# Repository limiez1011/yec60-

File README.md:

# yec60%

## Description
The yec60% keyboard is based on the ansi 60% layout and has 61 hotswappable sockets.

## Features
- Built in rp2040 MCU
- QMK firmware
- Hot swap sockets

## Flashing procedure
To flash firmware onto the RP2040 there are 2 pads under the "BOOT" text on the silkscreen, you must short those 2 pins to enter bootloader. Once in bootloader a drive should appear on your computer. Copy the .uf2 file from the QMK folder of the repo and paste it into the drive. Once done unplug the USB cable and plug it back in and it should be flashed.

## Credits
Credits to aio3 for his amazing tools for keyboard design, and his premade footprints. Some other people I'd love to thank is the QMK team which have created an amazing and easy to use system.

## BOM
|Name         |Purpose                        |Quantity|Total Cost (USD)|Link                                                                                                                                                                                                                                                                                                                                                                                                                                                                                                                                                                                                                                                                                            |Distributor|
|-------------|-------------------------------|--------|----------------|------------------------------------------------------------------------------------------------------------------------------------------------------------------------------------------------------------------------------------------------------------------------------------------------------------------------------------------------------------------------------------------------------------------------------------------------------------------------------------------------------------------------------------------------------------------------------------------------------------------------------------------------------------------------------------------------|-----------|
|stabilizers  |stabilizing                    |1       |11.00           |https://www.aliexpress.com/item/1005004229140548.html?spm=a2g0o.productlist.main.6.3e4b4e91M4QOD4&algo_pvid=52c0f35d-5f37-4dcc-980f-3d382011e670&pdp_ext_f=%7B%22order%22%3A%22103%22%2C%22spu_best_type%22%3A%22price%22%2C%22eval%22%3A%221%22%2C%22fromPage%22%3A%22search%22%7D&utparam-url=scene%3Asearch%7Cquery_from%3A%7Cx_object_id%3A1005004229140548%7C_p_origin_prod%3A                                                                                                                                                                                                                                                                                                             |aliexpress |
|keycaps      |keycaps                        |1       |16.50           |https://www.aliexpress.com/item/1005009426980407.html?spm=a2g0o.detail.pcDetailTopMoreOtherSeller.11.e5e56b47W8lzpD&gps-id=pcDetailTopMoreOtherSeller&scm=1007.40050.354490.0&scm_id=1007.40050.354490.0&scm-url=1007.40050.354490.0&pvid=6ae83b90-ce64-454f-894f-8b7744045ac3&_t=gps-id%3ApcDetailTopMoreOtherSeller%2Cscm-url%3A1007.40050.354490.0%2Cpvid%3A6ae83b90-ce64-454f-894f-8b7744045ac3%2Ctpp_buckets%3A668%232846%238110%231995&pdp_ext_f=%7B%22order%22%3A%22510%22%2C%22eval%22%3A%221%22%2C%22sceneId%22%3A%2230050%22%2C%22fromPage%22%3A%22recommend%22%7D&utparam-url=scene%3ApcDetailTopMoreOtherSeller%7Cquery_from%3A%7Cx_object_id%3A1005009426980407%7C_p_origin_prod%3A|aliexpress |
|switches     |gateron milky yellow|70      |26.50           |https://www.aliexpress.com/item/1005007039372956.html?spm=a2g0o.cart.0.0.bc85452cwC4OF7&mp=1                                                                                                                                                                                                                                                                                                                                                                                                                                                                                                                                                                                                    |aliexpress |
|PCB          |pcb                            |5       |30.00           |                                                                                                                                                                                                                                                                                                                                                                                                                                                                                                                                                                                                                                                                                                |JLCPCB     |
|kalih sockets|hotswap                        |61      |3.00            |https://www.lcsc.com/product-detail/C41430893.html?spm=wm.gwc.xh.13.cbm___wm.mxq.ssl.gwc&lcsc_vid=T1lbU1RRQwVWUQcCQgcLA1UAEgBbAwBUFFheBFAFEVAxVlNRTlhWUVZTQlBXUjsOAxUeFF5JWBEPFBcWGBMaSQgFBAJABAsLWA%3D%3D                                                                                                                                                                                                                                                                                                                                                                                                                                                                                      |LCSC       |
|2mb flash    |storage                        |1       |1.50            |https://www.lcsc.com/product-detail/C2986331.html?spm=wm.mxq.bom.8.xh___wm.bjg.btn.cre&lcsc_vid=T1lbU1RRQwVWUQcCQgcLA1UAEgBbAwBUFFheBFAFEVAxVlNRTlhWUVZTQlBXUjsOAxUeFF5JWBEPFBcWGBMaSQgFBAJABAsLWA%3D%3D                                                                                                                                                                                                                                                                                                                                                                                                                                                                                        |LCSC       |
|PASSIVES     |PASSIVING                      |1       |8.50            |                                                                                                                                                                                                                                                                                                                                                                                                                                                                                                                                                                                                                                                                                                |LCSC       |
|DIODES       |NKEY ROLLOVER                  |61      |4.00            |https://www.lcsc.com/product-detail/C81598.html?spm=wm.mxq.bom.14.xh___wm.bjg.btn.cre&lcsc_vid=T1lbU1RRQwVWUQcCQgcLA1UAEgBbAwBUFFheBFAFEVAxVlNRTlhWUVZTQlBXUjsOAxUeFF5JWBEPFBcWGBMaSQgFBAJABAsLWA%3D%3D                                                                                                                                                                                                                                                                                                                                                                                                                                                                                         |LCSC       |
|XTAL         |CLOCK                          |1       |1.00            |https://www.lcsc.com/product-detail/C9002.html?spm=wm.mxq.bom.12.xh___wm.bjg.btn.cre&lcsc_vid=T1lbU1RRQwVWUQcCQgcLA1UAEgBbAwBUFFheBFAFEVAxVlNRTlhWUVZTQlBXUjsOAxUeFF5JWBEPFBcWGBMaSQgFBAJABAsLWA%3D%3D                                                                                                                                                                                                                                                                                                                                                                                                                                                                                          |LCSC       |
|USBC         |PORT                           |1       |1.00            |https://www.lcsc.com/product-detail/C165948.html?spm=wm.mxq.bom.10.xh___wm.bjg.btn.cre&lcsc_vid=T1lbU1RRQwVWUQcCQgcLA1UAEgBbAwBUFFheBFAFEVAxVlNRTlhWUVZTQlBXUjsOAxUeFF5JWBEPFBcWGBMaSQgFBAJABAsLWA%3D%3D                                                                                                                                                                                                                                                                                                                                                                                                                                                                                        |LCSC       |
|RP2040       |MCU                            |1       |1.00            |https://www.lcsc.com/product-detail/C2040.html?spm=wm.mxq.bom.8.xh___wm.bjg.btn.cre&lcsc_vid=T1lbU1RRQwVWUQcCQgcLA1UAEgBbAwBUFFheBFAFEVAxVlNRTlhWUVZTQlBXUjsOAxUeFF5JWBEPFBcWGBMaSQgFBAJABAsLWA%3D%3D                                                                                                                                                                                                                                                                                                                                                                                                                                                                                           |LCSC       |
|RT9013-33GB  |LDO                            |1       |1.00            |https://www.lcsc.com/product-detail/C47773.html?spm=wm.mxq.bom.9.xh___wm.bjg.btn.cre&lcsc_vid=T1lbU1RRQwVWUQcCQgcLA1UAEgBbAwBUFFheBFAFEVAxVlNRTlhWUVZTQlBXUjsOAxUeFF5JWBEPFBcWGBMaSQgFBAJABAsLWA%3D%3D                                                                                                                                                                                                                                                                                                                                                                                                                                                                                          |LCSC       |

## Photos

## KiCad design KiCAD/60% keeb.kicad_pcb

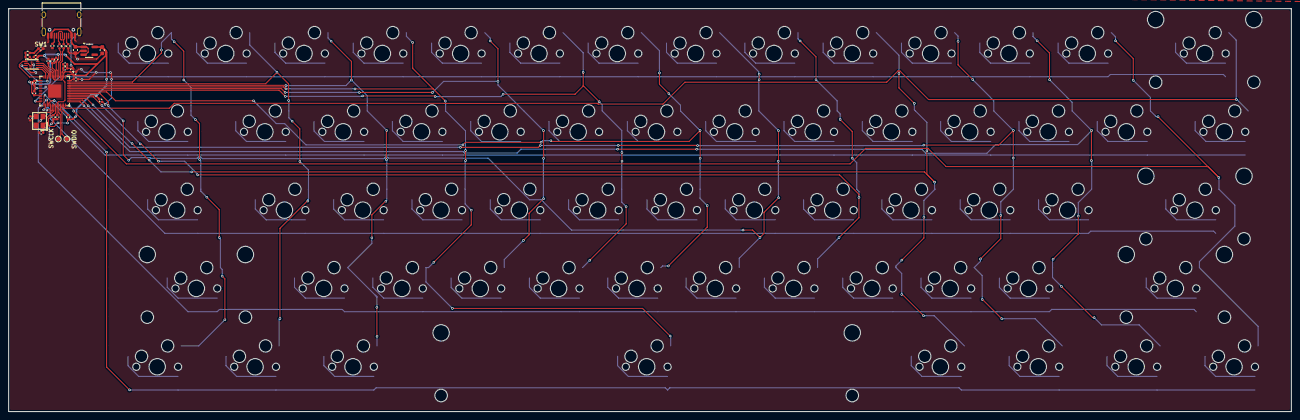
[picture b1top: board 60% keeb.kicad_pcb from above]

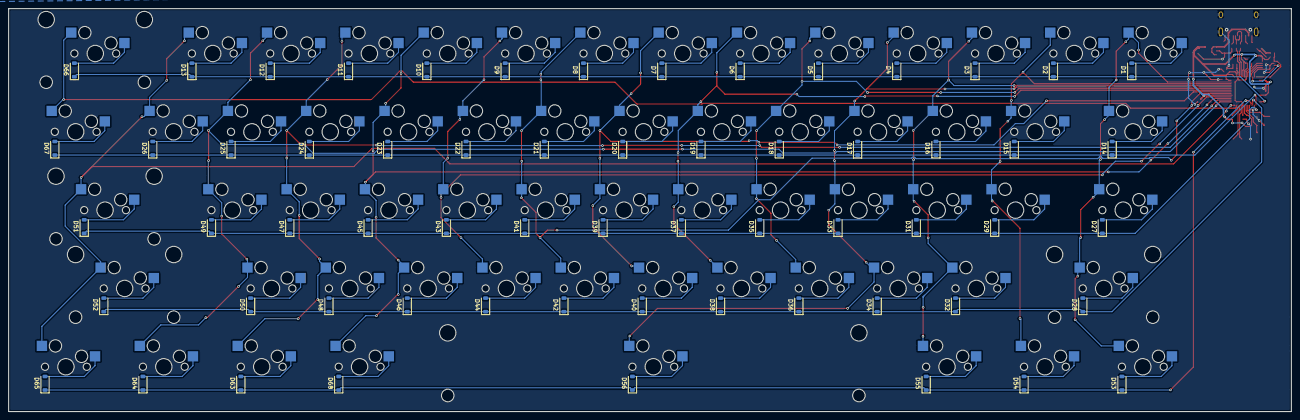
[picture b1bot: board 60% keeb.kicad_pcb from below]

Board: 2 copper layers, 312.0 x 98.0 mm, 155 parts (61 on the bottom side), 102 nets.

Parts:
C1, C2: 1uF; C_0603_1608Metric
C3, C12: 1uF; C_0402_1005Metric
C4, C5, C6, C7, C8, C9, C10, C11, C13, C14, C17, C19: 100nF; C_0402_1005Metric
C15, C16: 33pF; C_0402_1005Metric
D1, D2, D3, D4, D5, D6, D7, D8, D9, D10, D11, D12, D13, D14, D15, D16, D17, D18, D19, D20, D21, D22, D23, D24, D25, D26, D27, D28, D29, D31, D32, D33, D34, D35, D36, D37, D38, D39, D40, D41, D42, D43, D44, D45, D46, D47, D48, D49, D50, D51, D52, D53, D54, D55, D56, D63, D64, D65, D66, D67, D68: D_SOD-123
J1: USB_C_Receptacle_USB2.0_14P; USB_C_Receptacle_HRO_TYPE-C-31-M-12
R1, R2: 27; R_0402_1005Metric
R3, R4: 5.1K; R_0402_1005Metric
R5, R7: 10K; R_0402_1005Metric
R6: 1K; R_0402_1005Metric
SW1: SW_Push; C_0402_1005Metric_Pad0.74x0.62mm_HandSolder
SW2, SW3, SW4, SW5, SW6, SW7, SW8, SW9, SW10, SW11, SW12, SW13, SW14, SW16, SW17, SW18, SW19, SW20, SW21, SW22, SW23, SW24, SW25, SW26, SW27, SW28, SW29, SW30, SW31, SW32, SW33, SW34, SW35, SW36, SW37, SW38, SW39, SW40, SW41, SW44, SW45, SW46, SW47, SW48, SW49, SW50, SW51, SW52, SW53, SW55, SW56, SW57, SW59, SW60, SW61, SW62: MXOnly-1U-Hotswap
SW15, SW42, SW43: MXOnly-2U-Hotswap-ReversedStabilizers
SW54: MXOnly-2.75U-Hotswap-ReversedStabilizers
SW58: MXOnly-6.25U-Hotswap-ReversedStabilizers
TP1, TP2: TestPoint_Pad_D1.0mm
U1: RP2040; QFN-56-1EP_7x7mm_P0.4mm_EP3.2x3.2mm
U2: RT9013-33GB; SOT-23-5_HandSoldering
U3: W25Q128JVSIQ; Winbond_USON-8-1EP_3x2mm_P0.5mm_EP0.2x1.6mm
X1: X322512MSB4SI; CRYSTAL-SMD_4P-L3.2-W2.5-BL

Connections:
+1V1: C12.2, C13.2, C14.2, C19.2, U1.23 (DVDD), U1.45 (VREG_VOUT), U1.50 (DVDD)
+3.3V: C2.1, C3.2, C4.2, C5.2, C6.2, C7.2, C8.2, C9.2, C10.2, C11.2, C17.1, R5.1, R7.1, U1.1 (IOVDD), U1.10 (IOVDD), U1.22 (IOVDD), U1.33 (IOVDD), U1.42 (IOVDD), U1.43 (ADC_AVDD), U1.44 (VREG_VIN), U1.48 (USB_VDD), U1.49 (IOVDD), U2.5 (VOUT), U3.8 (VCC)
/CS: R5.2, R6.1, U1.56 (~QSPI_SS), U3.1 (/CS)
/D+: J1.A6 (D+), J1.B6 (D+), R2.1
/D-: J1.A7 (D-), J1.B7 (D-), R1.1
/DN: R1.2, U1.46 (USB_DM)
/DP: R2.2, U1.47 (USB_DP)
/SCLK: U1.52 (QSPI_SCLK), U3.6 (CLK)
/SD0: U1.53 (QSPI_SD0), U3.5 (DI(IO0))
/SD1: U1.55 (QSPI_SD1), U3.2 (DO(IO1))
/SD2: U1.54 (QSPI_SD2), U3.3 (/WP(IO2))
/SD3: U1.51 (QSPI_SD3), U3.7 (/HOLD/RESET(IO3))
/XIN: C15.2, U1.20 (XIN), X1.3 (OSC2)
/XOUT: C16.1, U1.21 (XOUT), X1.1 (OSC1)
COL0: SW2.2, SW16.2, SW30.2, SW43.2, SW55.2, U1.41 (GPIO29/ADC3)
COL1: SW3.2, SW17.2, SW31.2, SW56.2, U1.40 (GPIO28/ADC2)
COL2: SW4.2, SW18.2, SW32.2, SW44.2, SW57.2, U1.39 (GPIO27/ADC1)
COL3: SW5.2, SW19.2, SW33.2, SW45.2, SW58.2, U1.38 (GPIO26/ADC0)
COL4: SW6.2, SW20.2, SW34.2, SW46.2, U1.37 (GPIO25)
COL5: SW7.2, SW21.2, SW35.2, SW47.2, U1.36 (GPIO24)
COL6: SW8.2, SW22.2, SW36.2, SW48.2, U1.35 (GPIO23)
COL7: SW9.2, SW23.2, SW37.2, SW49.2, U1.34 (GPIO22)
COL8: SW10.2, SW24.2, SW38.2, SW50.2, U1.32 (GPIO21)
COL9: SW11.2, SW25.2, SW39.2, SW51.2, SW59.2, U1.31 (GPIO20)
COL10: SW12.2, SW26.2, SW40.2, SW52.2, SW60.2, U1.30 (GPIO19)
COL11: SW13.2, SW27.2, SW41.2, SW53.2, SW61.2, U1.29 (GPIO18)
COL12: SW14.2, SW28.2, SW42.2, SW54.2, SW62.2, U1.28 (GPIO17)
COL13: SW15.2, SW29.2, U1.27 (GPIO16)
GND: C1.1, C2.2, C3.1, C4.1, C5.1, C6.1, C7.1, C8.1, C9.1, C10.1, C11.1, C12.1, C13.1, C14.1, C15.1, C16.2, C17.2, C19.1, J1.A1 (GND), J1.A12 (GND), J1.B1 (GND), J1.B12 (GND), J1.SH (SHIELD), R3.2, R4.2, SW1.2, U1.19 (TESTEN), U1.57 (GND), U2.2 (GND), U3.4 (GND), U3.9, X1.2 (GND), X1.4 (GND)
unnamed: D1.2 (A), SW2.1
unnamed: D2.2 (A), SW3.1
unnamed: D3.2 (A), SW4.1
unnamed: D4.2 (A), SW5.1
unnamed: D5.2 (A), SW6.1
unnamed: D6.2 (A), SW7.1
unnamed: D7.2 (A), SW8.1
unnamed: D8.2 (A), SW9.1
unnamed: D9.2 (A), SW10.1
unnamed: D10.2 (A), SW11.1
unnamed: D11.2 (A), SW12.1
unnamed: D12.2 (A), SW13.1
unnamed: D13.2 (A), SW14.1
unnamed: D14.2 (A), SW16.1
unnamed: D15.2 (A), SW17.1
unnamed: D16.2 (A), SW18.1
unnamed: D17.2 (A), SW19.1
unnamed: D18.2 (A), SW20.1
unnamed: D19.2 (A), SW21.1
unnamed: D20.2 (A), SW22.1
unnamed: D21.2 (A), SW23.1
unnamed: D22.2 (A), SW24.1
unnamed: D23.2 (A), SW25.1
unnamed: D24.2 (A), SW26.1
unnamed: D25.2 (A), SW27.1
unnamed: D26.2 (A), SW28.1
unnamed: D27.2 (A), SW30.1
unnamed: D28.2 (A), SW43.1
unnamed: D29.2 (A), SW31.1
unnamed: D31.2 (A), SW32.1
unnamed: D32.2 (A), SW44.1
unnamed: D33.2 (A), SW33.1
unnamed: D34.2 (A), SW45.1
unnamed: D35.2 (A), SW34.1
unnamed: D36.2 (A), SW46.1
unnamed: D37.2 (A), SW35.1
unnamed: D38.2 (A), SW47.1
unnamed: D39.2 (A), SW36.1
unnamed: D40.2 (A), SW48.1
unnamed: D41.2 (A), SW37.1
unnamed: D42.2 (A), SW49.1
unnamed: D43.2 (A), SW38.1
unnamed: D44.2 (A), SW50.1
unnamed: D45.2 (A), SW39.1
unnamed: D46.2 (A), SW51.1
unnamed: D47.2 (A), SW40.1
unnamed: D48.2 (A), SW52.1
unnamed: D49.2 (A), SW41.1
unnamed: D50.2 (A), SW53.1
unnamed: D51.2 (A), SW42.1
unnamed: D52.2 (A), SW54.1
unnamed: D53.2 (A), SW55.1
unnamed: D54.2 (A), SW56.1
unnamed: D55.2 (A), SW57.1
unnamed: D56.2 (A), SW58.1
unnamed: D63.2 (A), SW60.1
unnamed: D64.2 (A), SW61.1
unnamed: D65.2 (A), SW62.1
unnamed: D66.2 (A), SW15.1
unnamed: D67.2 (A), SW29.1
unnamed: D68.2 (A), SW59.1
unnamed: J1.A5 (CC1), R3.1
unnamed: J1.B5 (CC2), R4.1
unnamed: R6.2, SW1.1
unnamed: R7.2, U1.26 (RUN)
unnamed: TP1.1 (1_1), U1.24 (SWCLK)
unnamed: TP2.1 (1_1), U1.25 (SWDIO)
ROW0: D1.1 (K), D2.1 (K), D3.1 (K), D4.1 (K), D5.1 (K), D6.1 (K), D7.1 (K), D8.1 (K), D9.1 (K), D10.1 (K), D11.1 (K), D12.1 (K), D13.1 (K), D66.1 (K), U1.14 (GPIO11)
ROW1: D14.1 (K), D15.1 (K), D16.1 (K), D17.1 (K), D18.1 (K), D19.1 (K), D20.1 (K), D21.1 (K), D22.1 (K), D23.1 (K), D24.1 (K), D25.1 (K), D26.1 (K), D67.1 (K), U1.15 (GPIO12)
ROW2: D27.1 (K), D29.1 (K), D31.1 (K), D33.1 (K), D35.1 (K), D37.1 (K), D39.1 (K), D41.1 (K), D43.1 (K), D45.1 (K), D47.1 (K), D49.1 (K), D51.1 (K), U1.16 (GPIO13)
ROW3: D28.1 (K), D32.1 (K), D34.1 (K), D36.1 (K), D38.1 (K), D40.1 (K), D42.1 (K), D44.1 (K), D46.1 (K), D48.1 (K), D50.1 (K), D52.1 (K), U1.17 (GPIO14)
ROW4: D53.1 (K), D54.1 (K), D55.1 (K), D56.1 (K), D63.1 (K), D64.1 (K), D65.1 (K), D68.1 (K), U1.18 (GPIO15)
VBUS: C1.2, J1.A4 (VBUS), J1.A9 (VBUS), J1.B4 (VBUS), J1.B9 (VBUS), U2.1 (VIN), U2.3 (EN)

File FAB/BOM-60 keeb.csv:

Comment,Designator,Footprint,LCSC,Quantity
100nF,"C10,C11,C13,C14,C17,C19,C4,C5,C6,C7,C8,C9",C_0402_1005Metric,C1525,12
10K,"R5,R7",R_0402_1005Metric,C25744,2
1K,R6,R_0402_1005Metric,C11702,1
1uF,"C1,C2",C_0603_1608Metric,C15849,2
1uF,"C12,C3",C_0402_1005Metric,C52923,2
27,"R1,R2",R_0402_1005Metric,C25156,2
33pF,"C15,C16",C_0402_1005Metric,C1562,2
5.1K,"R3,R4",R_0402_1005Metric,C25905,2
RP2040,U1,QFN-56-1EP_7x7mm_P0.4mm_EP3.2x3.2mm,C2040,1
RT9013-33GB,U2,SOT-23-5_HandSoldering,C47773,1
USB_C_Receptacle_USB2.0_14P,J1,USB_C_Receptacle_HRO_TYPE-C-31-M-12,C165948,1
W25Q128JVSIQ,U3,Winbond_USON-8-1EP_3x2mm_P0.5mm_EP0.2x1.6mm,C2986331,1
X322512MSB4SI,X1,CRYSTAL-SMD_4P-L3.2-W2.5-BL,C9002,1
~,"SW10,SW11,SW12,SW13,SW14,SW15,SW16,SW17,SW18,SW19,SW2,SW20,SW21,SW22,SW23,SW24,SW25,SW26,SW27,SW28,SW29,SW3,SW30,SW31,SW32,SW33,SW34,SW35,SW36,SW37,SW38,SW39,SW4,SW40,SW41,SW42,SW43,SW44,SW45,SW46,SW47,SW48,SW49,SW5,SW50,SW51,SW52,SW53,SW54,SW55,SW56,SW57,SW58,SW59,SW6,SW60,SW61,SW62,SW7,SW8,SW9",MXOnly-1U-Hotswap,C41430893,61
~,"D1,D10,D11,D12,D13,D14,D15,D16,D17,D18,D19,D2,D20,D21,D22,D23,D24,D25,D26,D27,D28,D29,D3,D31,D32,D33,D34,D35,D36,D37,D38,D39,D4,D40,D41,D42,D43,D44,D45,D46,D47,D48,D49,D5,D50,D51,D52,D53,D54,D55,D56,D6,D63,D64,D65,D66,D67,D68,D7,D8,D9",D_SOD-123,C81598,61
~,TP2,TestPoint_Pad_D1.0mm,,1
~,TP1,TestPoint_Pad_D1.0mm,,1
SW_Push,SW1,C_0402_1005Metric_Pad0.74x0.62mm_HandSolder,,1

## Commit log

2026-05-24 Create x
2026-05-26 Create keybard
2026-05-26 Rename keybard to keybard.step
2026-05-28 Update README with flashing procedure and credits
    Added flashing procedure and credits sections to README.
2026-06-16 Update BOM with new components and details
    Added new components to the BOM including stabilizers and keycaps with links and costs.
2026-06-16 Update switches from cherry mx red to gateron milky yellow
2026-06-16 Add additional images to README
